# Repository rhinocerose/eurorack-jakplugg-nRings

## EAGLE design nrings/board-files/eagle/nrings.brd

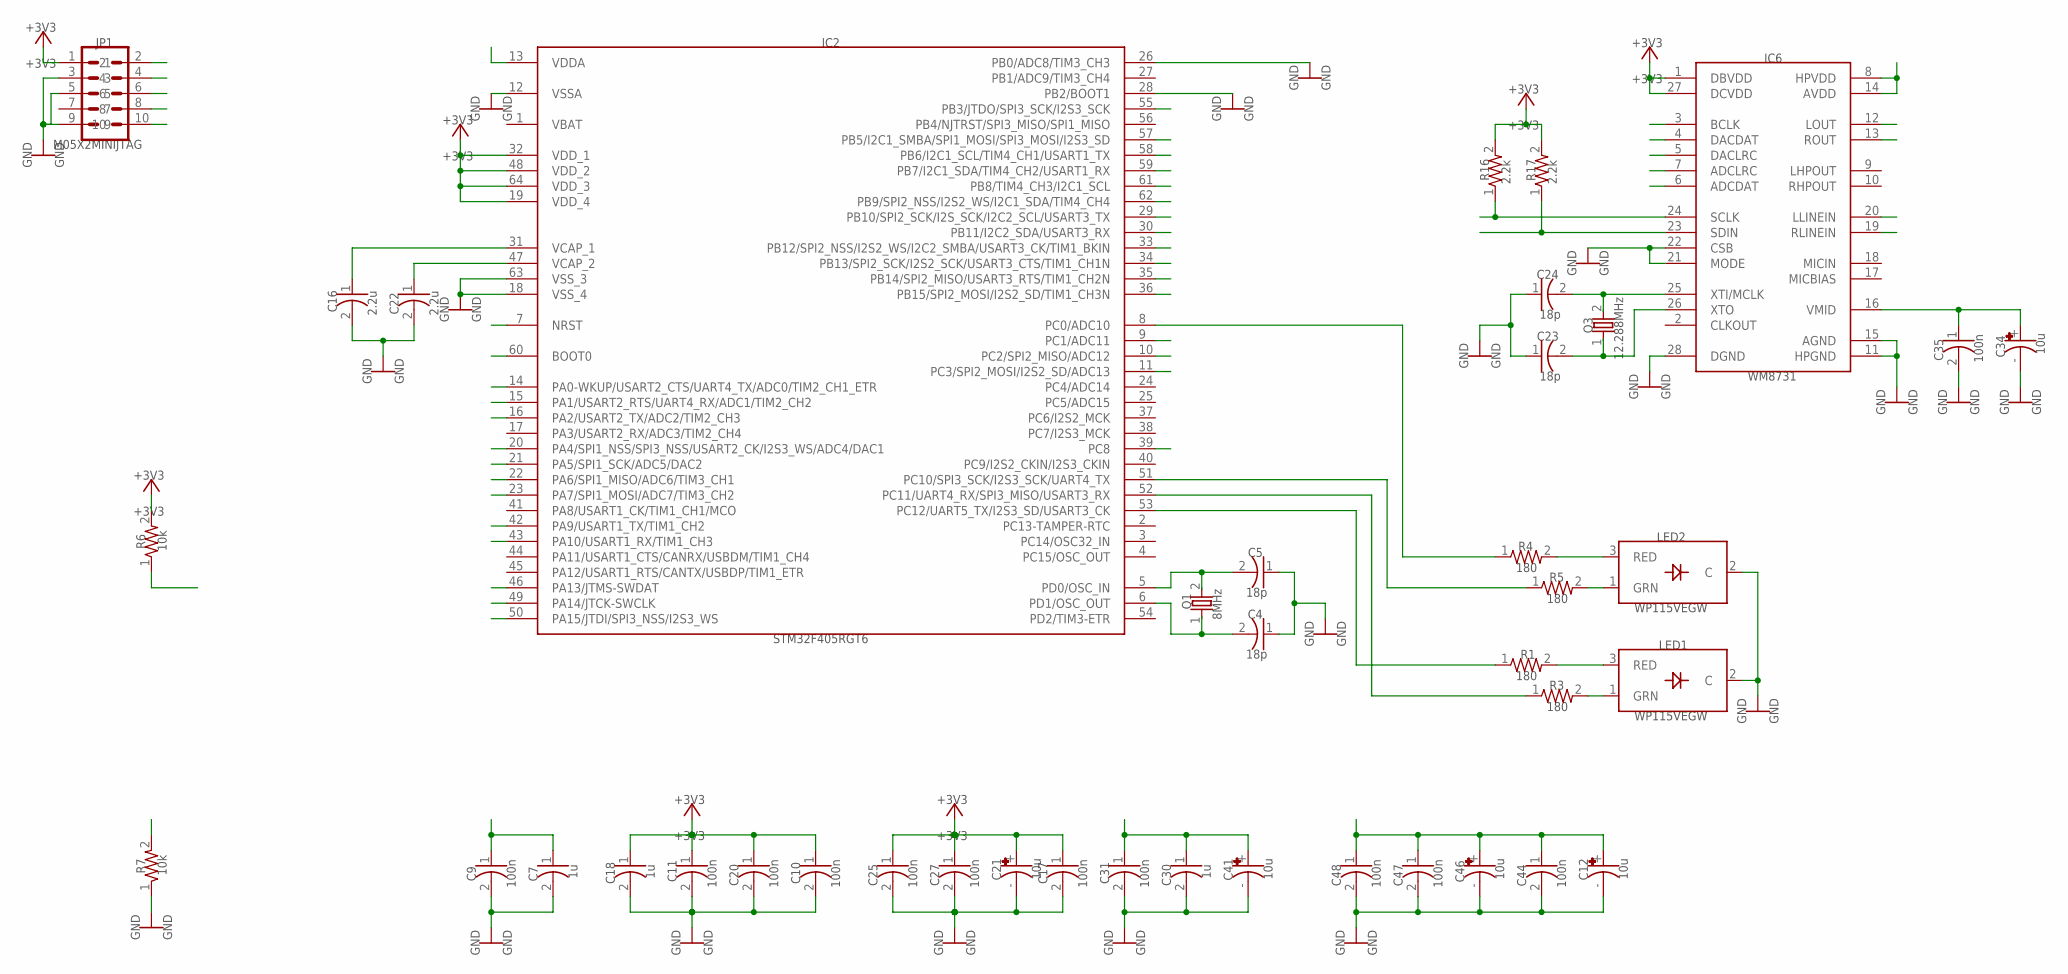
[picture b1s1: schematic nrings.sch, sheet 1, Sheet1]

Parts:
C4, C5, C23, C24: 18p; CAP_0603
C7, C18, C30: 1u; CAP_0603
C9, C10, C11, C17, C20, C25, C27, C31, C35, C44, C47, C48: 100n; CAP_0603
C12, C21, C34, C41, C46: 10u; PANASONIC_A
C16, C22: 2.2u; CAP_0805
IC2: STM32F405RGT6; TQFP-10X10-64
IC6: WM8731; SSOP28
JP1: M05X2MINIJTAG; 2X5-1.27
LED1, LED2: WP115VEGW; LED-BICOLOR-THROUGHHOLE
Q1: 8MHz; TSC_7A_CRYSTAL
Q3: 12.288MHz; TSC_7A_CRYSTAL
R1, R3, R4, R5: 180; RES_0603
R6, R7: 10k; RES_0603
R16, R17: 2.2k; RES_0603

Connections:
+3V3: C10.1, C11.1, C17.1, C18.1, C20.1, C21.+, C25.1, C27.1, IC2.19 (VDD_4), IC2.32 (VDD_1), IC2.48 (VDD_2), IC2.64 (VDD_3), IC6.1 (DBVDD), IC6.27 (DCVDD), JP1.1, R6.2, R16.2, R17.2; also elsewhere on the board
+3V3_A: C7.1, C9.1, C12.+, C30.1, C31.1, C41.+, C44.1, C46.+, C47.1, C48.1, IC2.13 (VDDA), IC6.8 (HPVDD), IC6.14 (AVDD); also elsewhere on the board
AUX_OUT: IC6.13 (ROUT); also elsewhere on the board
BOOT_FLASH: IC2.60 (BOOT0), R7.2
BRIGHTNESS_CV: IC2.14 (PA0-WKUP/USART2_CTS/UART4_TX/ADC0/TIM2_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); also elsewhere on the board
DAMP_CV: IC2.21 (PA5/SPI1_SCK/ADC5/DAC2); also elsewhere on the board
FM_CV: IC2.20 (PA4/SPI1_NSS/SPI3_NSS/USART2_CK/I2S3_WS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); also elsewhere on the board
FREQUENCY_POT: IC2.11 (PC3/SPI2_MOSI/I2S2_SD/ADC13); also elsewhere on the board
GEOMETRY_CV: IC2.22 (PA6/SPI1_MISO/ADC6/TIM3_CH1); also elsewhere on the board
GEOMETRY_POT: IC2.10 (PC2/SPI2_MISO/ADC12); also elsewhere on the board
GND: C4.1, C5.1, C7.2, C9.2, C10.2, C11.2, C12.-, C16.2, C17.2, C18.2, C20.2, C21.-, C22.2, C23.1, C24.1, C25.2, C27.2, C30.2, C31.2, C34.-, C35.2, C41.-, C44.2, C46.-, C47.2, C48.2, IC2.12 (VSSA), IC2.18 (VSS_4), IC2.26 (PB0/ADC8/TIM3_CH3), IC2.28 (PB2/BOOT1), IC2.63 (VSS_3), IC6.11 (HPGND), IC6.15 (AGND), IC6.21 (MODE), IC6.22 (CSB), IC6.28 (DGND), JP1.3, JP1.5, JP1.9, LED1.2 (C), LED2.2 (C), R7.1; also elsewhere on the board
I2C_SCL: IC2.29 (PB10/SPI2_SCK/I2S_SCK/I2C2_SCL/USART3_TX), IC6.24 (SCLK), R16.1
I2C_SDA: IC2.30 (PB11/I2C2_SDA/USART3_RX), IC6.23 (SDIN), R17.1
I2S_LRCK: IC2.33 (PB12/SPI2_NSS/I2S2_WS/I2C2_SMBA/USART3_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), IC6.5 (DACLRC), IC6.7 (ADCLRC)
I2S_SCK: IC2.34 (PB13/SPI2_SCK/I2S2_SCK/USART3_CTS/TIM1_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), IC6.3 (BCLK)
I2S_SIN: IC2.35 (PB14/SPI2_MISO/USART3_RTS/TIM1_CH2N), IC6.6 (ADCDAT)
I2S_SOUT: IC2.36 (PB15/SPI2_MOSI/I2S2_SD/TIM1_CH3N), IC6.4 (DACDAT)
IN_1: IC6.20 (LLINEIN); also elsewhere on the board
IN_2: IC6.19 (RLINEIN); also elsewhere on the board
JTCK: IC2.49 (PA14/JTCK-SWCLK), JP1.4
JTDI: IC2.50 (PA15/JTDI/SPI3_NSS/I2S3_WS), JP1.8
JTDO: IC2.55 (PB3/JTDO/SPI3_SCK/I2S3_SCK), JP1.6
JTMS: IC2.46 (PA13/JTMS-SWDAT), JP1.2
MAIN_OUT: IC6.12 (LOUT); also elsewhere on the board
MUXED_POTS: IC2.9 (PC1/ADC11); also elsewhere on the board
MUX_ADDR_0: IC2.59 (PB7/I2C1_SDA/TIM4_CH2/USART1_RX); also elsewhere on the board
MUX_ADDR_1: IC2.58 (PB6/I2C1_SCL/TIM4_CH1/USART1_TX); also elsewhere on the board
MUX_ADDR_2: IC2.57 (PB5/I2C1_SMBA/SPI1_MOSI/SPI3_MOSI/I2S3_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); also elsewhere on the board
unnamed: C5.2, IC2.5 (PD0/OSC_IN), Q1.2
unnamed: C4.2, IC2.6 (PD1/OSC_OUT), Q1.1
unnamed: LED1.3 (RED), R1.2
unnamed: C22.1, IC2.47 (VCAP_2)
unnamed: C34.+, C35.1, IC6.16 (VMID)
unnamed: C16.1, IC2.31 (VCAP_1)
unnamed: LED1.1 (GRN), R3.2
unnamed: LED2.3 (RED), R4.2
unnamed: LED2.1 (GRN), R5.2
unnamed: IC2.52 (PC11/UART4_RX/SPI3_MISO/USART3_RX), R3.1
unnamed: IC2.8 (PC0/ADC10), R4.1
unnamed: C24.2, IC6.25 (XTI/MCLK), Q3.2
unnamed: C23.2, IC6.26 (XTO), Q3.1
unnamed: IC2.53 (PC12/UART5_TX/I2S3_SD/USART3_CK), R1.1
unnamed: IC2.51 (PC10/SPI3_SCK/I2S3_SCK/UART4_TX), R5.1
NORMALIZATION_PROBE: IC2.39 (PC8); also elsewhere on the board
POSITION_CV: IC2.23 (PA7/SPI1_MOSI/ADC7/TIM3_CH2); also elsewhere on the board
RESET: IC2.7 (NRST), JP1.10, R6.1
STRUM: IC2.16 (PA2/USART2_TX/ADC2/TIM2_CH3); also elsewhere on the board
SW_MODE: IC2.61 (PB8/TIM4_CH3/I2C1_SCL); also elsewhere on the board
SW_POLYPHONY: IC2.62 (PB9/SPI2_NSS/I2S2_WS/I2C1_SDA/TIM4_CH4); also elsewhere on the board
V_OCT_CV: IC2.15 (PA1/USART2_RTS/UART4_RX/ADC1/TIM2_CH2); also elsewhere on the board

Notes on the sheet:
+3V3
18p
100n
C10
C11
C12
10u
C16
2.2u
C17
C18
C20
C21
C22
C23
C24
C25
C27
C30
C31
C34
C35
C41
C44
C46
C47
C48
GND
IC2
STM32F405RGT6
IC6
WM8731
JP1
M05X2MINIJTAG
LED1
WP115VEGW
LED2
8MHz
12.288MHz
180

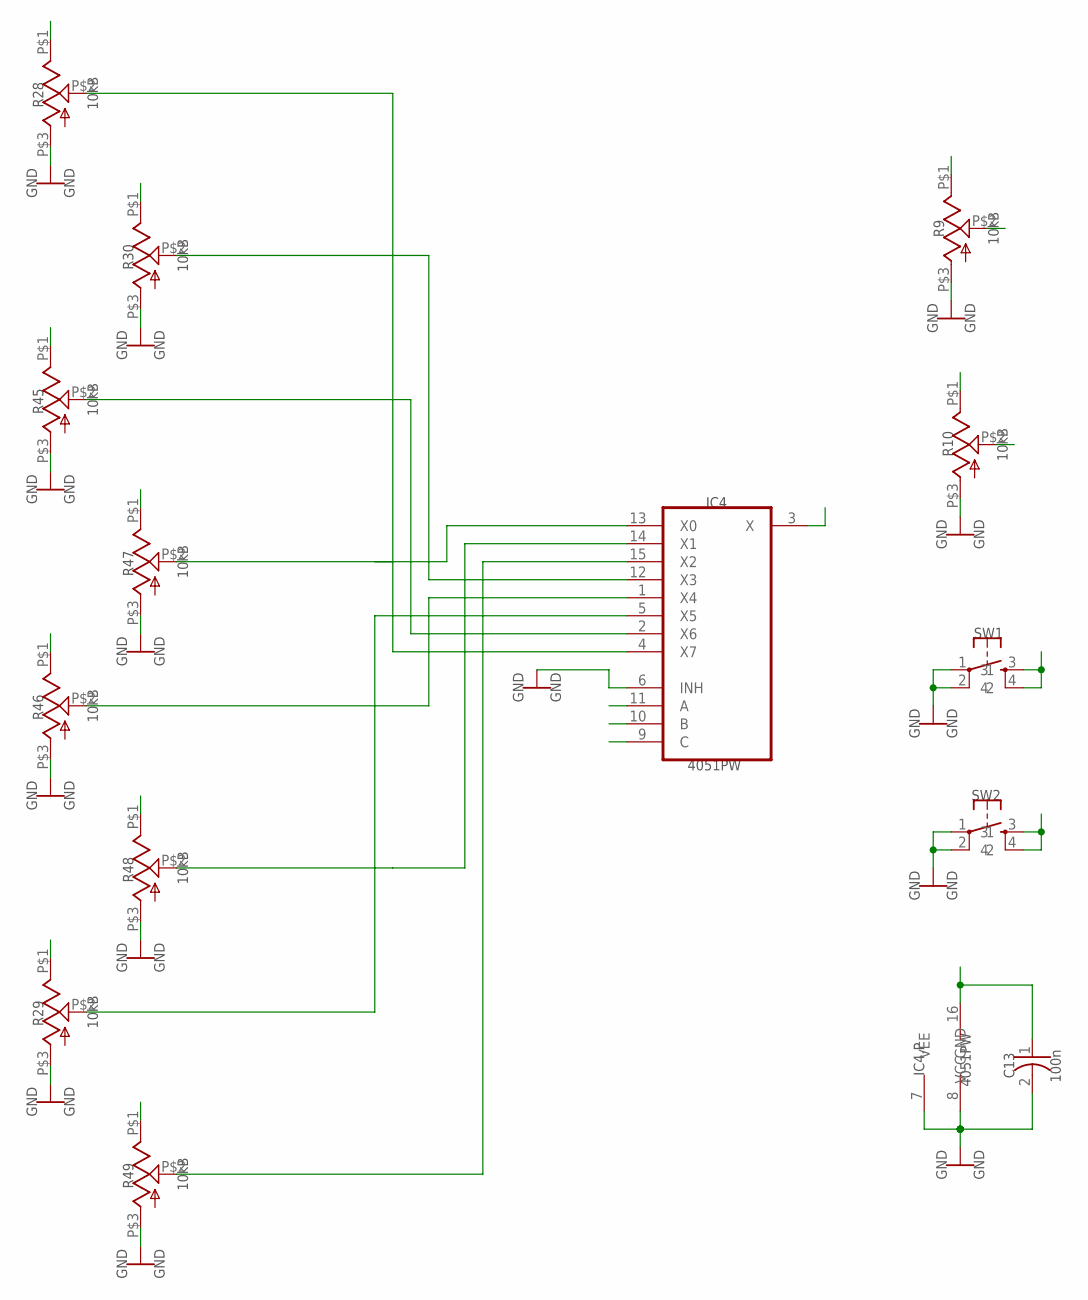
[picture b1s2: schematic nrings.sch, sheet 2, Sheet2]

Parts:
C13: 100n; CAP_0603
IC4: 4051PW; TSSOP16
R9, R10, R28, R29, R30: 10kB; ALPS_POT_VERTICAL_PS
R45, R46, R47, R48, R49: 10kB; ALPS_POT_VERTICAL
SW1, SW2: TAC_SWITCHPTH; TACTILE-PTH

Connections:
+3V3_A: C13.1, IC4.16 (VCC), R9.P$1 (E), R10.P$1 (E), R28.P$1 (E), R29.P$1 (E), R30.P$1 (E), R45.P$1 (E), R46.P$1 (E), R47.P$1 (E), R48.P$1 (E), R49.P$1 (E); also elsewhere on the board
BRIGHTNESS_ATT: IC4.2 (X6), R45.P$2 (S)
BRIGHTNESS_POT: IC4.4 (X7), R28.P$2 (S)
DAMP_ATT: IC4.13 (X0), R47.P$2 (S)
DAMP_POT: IC4.5 (X5), R29.P$2 (S)
FREQUENCY_ATT: IC4.1 (X4), R46.P$2 (S)
FREQUENCY_POT: R9.P$2 (S); also elsewhere on the board
GEOMETRY_ATT: IC4.14 (X1), R48.P$2 (S)
GEOMETRY_POT: R10.P$2 (S); also elsewhere on the board
GND: C13.2, IC4.6 (INH), IC4.7 (VEE), IC4.8 (GND), R9.P$3 (A), R9.P$4, R9.P$5, R10.P$3 (A), R10.P$4, R10.P$5, R28.P$3 (A), R28.P$4, R28.P$5, R29.P$3 (A), R29.P$4, R29.P$5, R30.P$3 (A), R30.P$4, R30.P$5, R45.P$3 (A), R45.P$4, R45.P$5, R46.P$3 (A), R46.P$4, R46.P$5, R47.P$3 (A), R47.P$4, R47.P$5, R48.P$3 (A), R48.P$4, R48.P$5, R49.P$3 (A), R49.P$4, R49.P$5, SW1.1, SW1.2, SW2.1, SW2.2; also elsewhere on the board
MUXED_POTS: IC4.3 (X); also elsewhere on the board
MUX_ADDR_0: IC4.11 (A); also elsewhere on the board
MUX_ADDR_1: IC4.10 (B); also elsewhere on the board
MUX_ADDR_2: IC4.9 (C); also elsewhere on the board
POSITION_ATT: IC4.15 (X2), R49.P$2 (S)
POSITION_POT: IC4.12 (X3), R30.P$2 (S)
SW_MODE: SW2.3, SW2.4; also elsewhere on the board
SW_POLYPHONY: SW1.3, SW1.4; also elsewhere on the board

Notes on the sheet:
C13
100n
GND
IC4
4051PW
IC4.P
10kB
R10
R28
R29
R30
R45
R46
R47
R48
R49
SW1
SW2

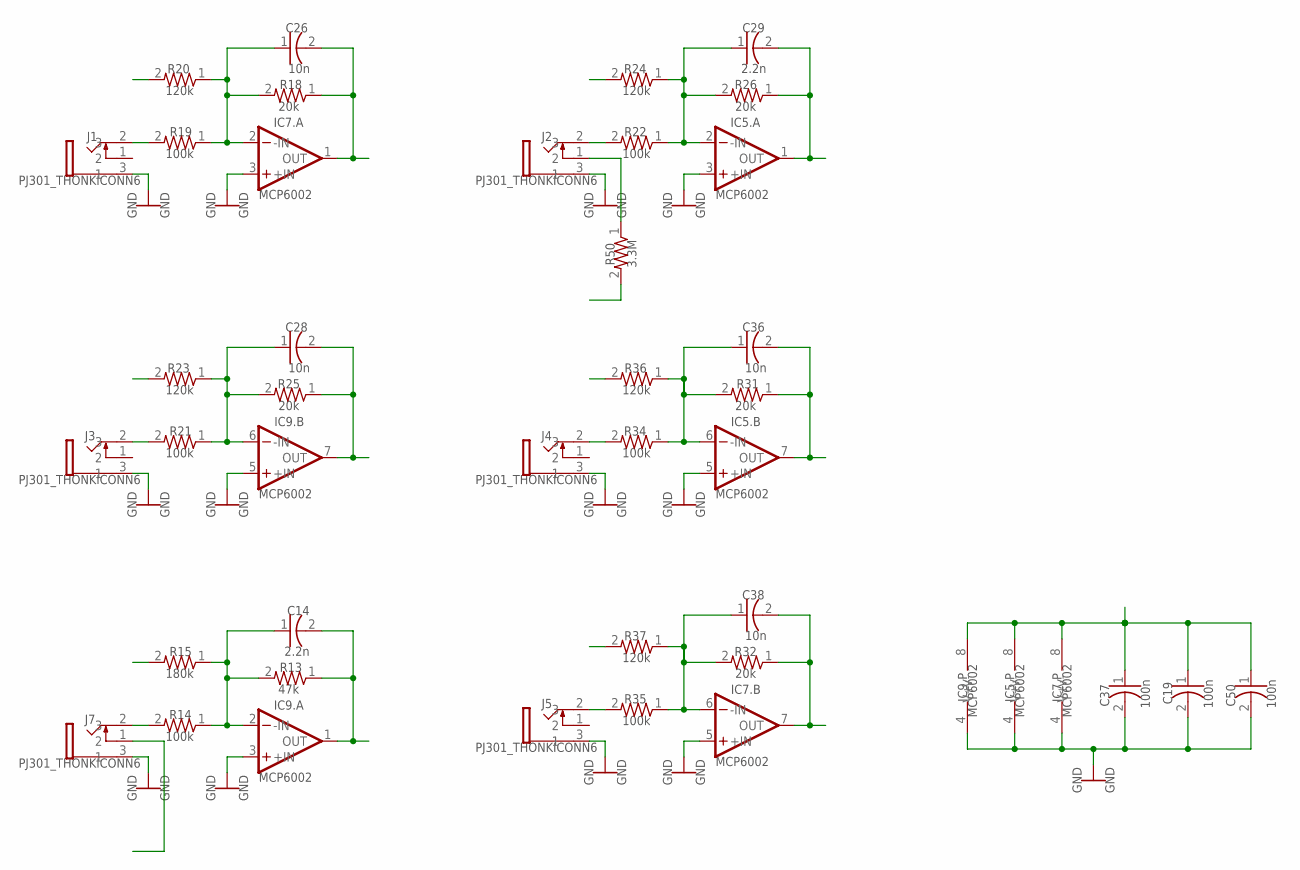
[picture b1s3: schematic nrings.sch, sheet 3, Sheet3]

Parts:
C14, C29: 2.2n; CAP_0603
C19, C37, C50: 100n; CAP_0603
C26, C28, C36, C38: 10n; CAP_0603
IC5, IC7, IC9: MCP6002; SO08
J1, J2, J3, J4, J5, J7: PJ301_THONKICONN6; THONKICONN
R13: 47k; RES_0603
R14, R19, R21, R22, R34, R35: 100k; RES_0603
R15: 180k; RES_0603
R18, R25, R26, R31, R32: 20k; RES_0603
R20, R23, R24, R36, R37: 120k; RES_0603
R50: 3.3M; RES_0603

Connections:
+3V3_A: C19.1, C37.1, C50.1, IC5.8 (V+), IC7.8 (V+), IC9.8 (V+), R50.2; also elsewhere on the board
AREF_-10: R15.2, R20.2, R23.2, R24.2, R36.2, R37.2; also elsewhere on the board
BRIGHTNESS_CV: C26.2, IC7.1 (OUT), R18.1; also elsewhere on the board
CV_NORMALIZATION: J7.1 (2); also elsewhere on the board
DAMP_CV: C28.2, IC9.7 (OUT), R25.1; also elsewhere on the board
FM_CV: C29.2, IC5.1 (OUT), R26.1; also elsewhere on the board
GEOMETRY_CV: C36.2, IC5.7 (OUT), R31.1; also elsewhere on the board
GND: C19.2, C37.2, C50.2, IC5.3 (+IN), IC5.4 (V-), IC5.5 (+IN), IC7.3 (+IN), IC7.4 (V-), IC7.5 (+IN), IC9.3 (+IN), IC9.4 (V-), IC9.5 (+IN), J1.3 (1), J2.3 (1), J3.3 (1), J4.3 (1), J5.3 (1), J7.3 (1); also elsewhere on the board
unnamed: J1.2 (3), R19.2
unnamed: C26.1, IC7.2 (-IN), R18.2, R19.1, R20.1
unnamed: J7.2 (3), R14.2
unnamed: J2.2 (3), R22.2
unnamed: C29.1, IC5.2 (-IN), R22.1, R24.1, R26.2
unnamed: J4.2 (3), R34.2
unnamed: J3.2 (3), R21.2
unnamed: C28.1, IC9.6 (-IN), R21.1, R23.1, R25.2
unnamed: C14.1, IC9.2 (-IN), R13.2, R14.1, R15.1
unnamed: C36.1, IC5.6 (-IN), R31.2, R34.1, R36.1
unnamed: J5.2 (3), R35.2
unnamed: C38.1, IC7.6 (-IN), R32.2, R35.1, R37.1
unnamed: J2.1 (2), R50.1
POSITION_CV: C38.2, IC7.7 (OUT), R32.1; also elsewhere on the board
V_OCT_CV: C14.2, IC9.1 (OUT), R13.1; also elsewhere on the board

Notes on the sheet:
C14
2.2n
C19
100n
C26
10n
C28
C29
C36
C37
C38
C50
GND
IC5.A
MCP6002
IC5.B
IC5.P
IC7.A
IC7.B
IC7.P
IC9.A
IC9.B
IC9.P
PJ301_THONKICONN6
R13
47k
R14
100k
R15
180k
R18
20k
R19
R20
120k
R21
R22
R23
R24
R25

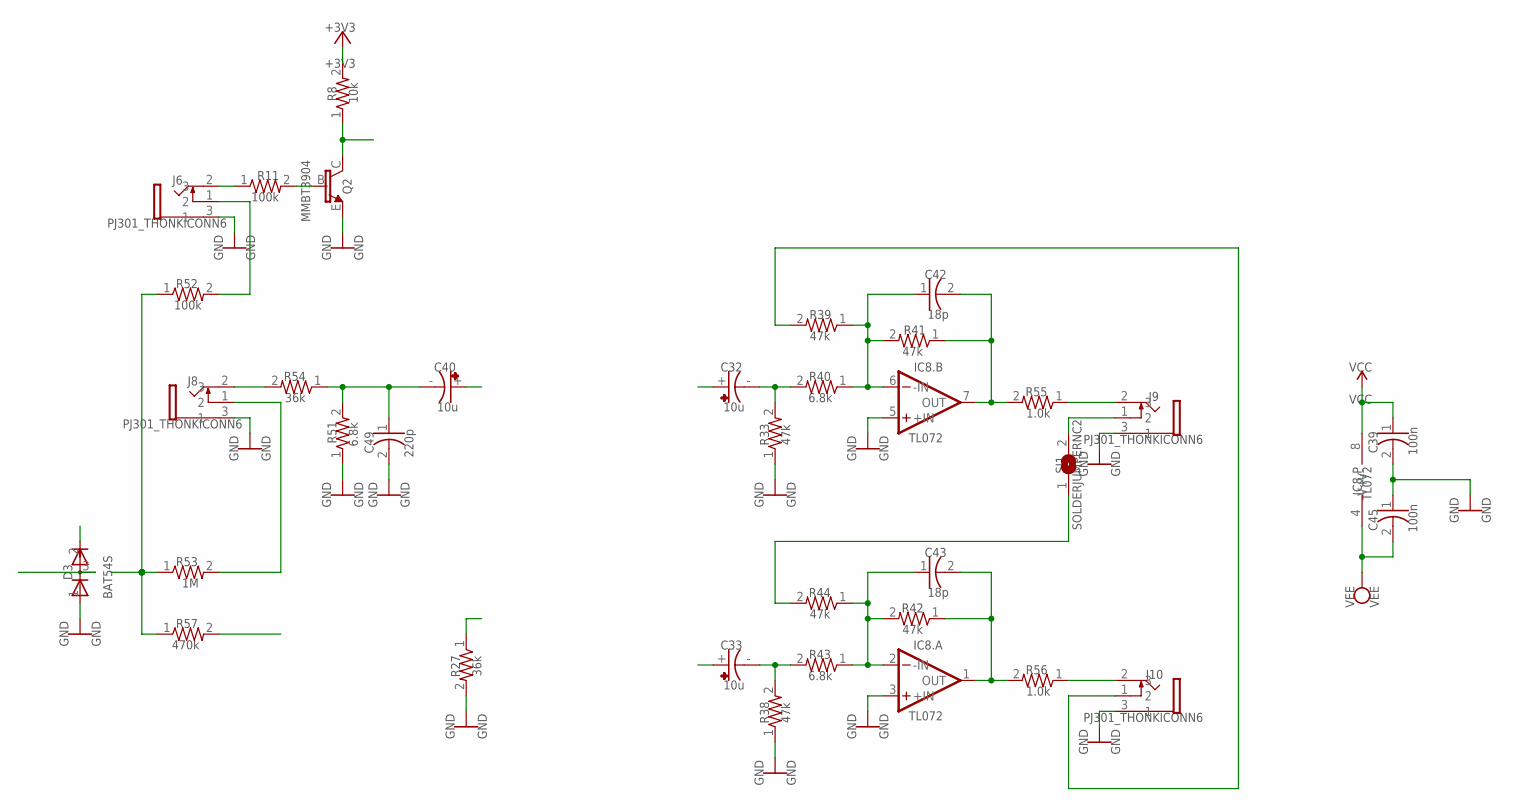
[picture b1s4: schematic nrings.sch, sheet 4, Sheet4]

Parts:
C32, C33, C40: 10u; PANASONIC_A
C39, C45: 100n; CAP_0603
C42, C43: 18p; CAP_0603
C49: 220p; CAP_0603
D3: BAT54S; SOT23
IC8: TL072; SO08
J6, J8, J9, J10: PJ301_THONKICONN6; THONKICONN
Q2: MMBT3904; SOT23-BEC
R8: 10k; RES_0603
R11, R52: 100k; RES_0603
R27, R54: 36k; RES_0603
R33, R38, R39, R41, R42, R44: 47k; RES_0603
R40, R43, R51: 6.8k; RES_0603
R53: 1M; RES_0603
R55, R56: 1.0k; RES_0603
R57: 470k; RES_0603
SJ1: SOLDERJUMPERNC2; SJ_2S-NOTRACE

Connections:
+3V3: D3.2 (C), R8.2; also elsewhere on the board
AUX_OUT: C33.+; also elsewhere on the board
CV_NORMALIZATION: R57.2; also elsewhere on the board
GND: C39.2, C45.1, C49.2, D3.1 (A), IC8.3 (+IN), IC8.5 (+IN), J6.3 (1), J8.3 (1), J9.3 (1), J10.3 (1), Q2.E, R27.2, R33.1, R38.1, R51.1; also elsewhere on the board
IN_1: R27.1; also elsewhere on the board
IN_2: C40.+; also elsewhere on the board
MAIN_OUT: C32.+; also elsewhere on the board
unnamed: J6.2 (3), R11.1
unnamed: C40.-, C49.1, R51.2, R54.1
unnamed: J6.1 (2), R52.2
unnamed: J8.2 (3), R54.2
unnamed: C33.-, R38.2, R43.2
unnamed: C43.1, IC8.2 (-IN), R42.2, R43.1, R44.1
unnamed: C43.2, IC8.1 (OUT), R42.1, R56.2
unnamed: J10.2 (3), R56.1
unnamed: C32.-, R33.2, R40.2
unnamed: C42.1, IC8.6 (-IN), R39.1, R40.1, R41.2
unnamed: C42.2, IC8.7 (OUT), R41.1, R55.2
unnamed: J9.2 (3), R55.1
unnamed: J8.1 (2), R53.2
unnamed: J10.1 (2), R39.2
unnamed: R44.2, SJ1.1
unnamed: J9.1 (2), SJ1.2
unnamed: Q2.B, R11.2
NORMALIZATION_PROBE: D3.3 (AC), R52.1, R53.1, R57.1; also elsewhere on the board
STRUM: Q2.C, R8.1; also elsewhere on the board
VCC: C39.1, IC8.8 (V+); also elsewhere on the board
VEE: C45.2, IC8.4 (V-); also elsewhere on the board

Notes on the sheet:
+3V3
C32
10u
C33
C39
100n
C40
C42
18p
C43
C45
C49
220p
BAT54S
GND
IC8.A
TL072
IC8.B
IC8.P
PJ301_THONKICONN6
J10
VCC
MMBT3904
10k
R11
100k
R27
36k
R33
47k
R38
R39
R40
6.8k
R41
R42
R43
R44
R51
R52

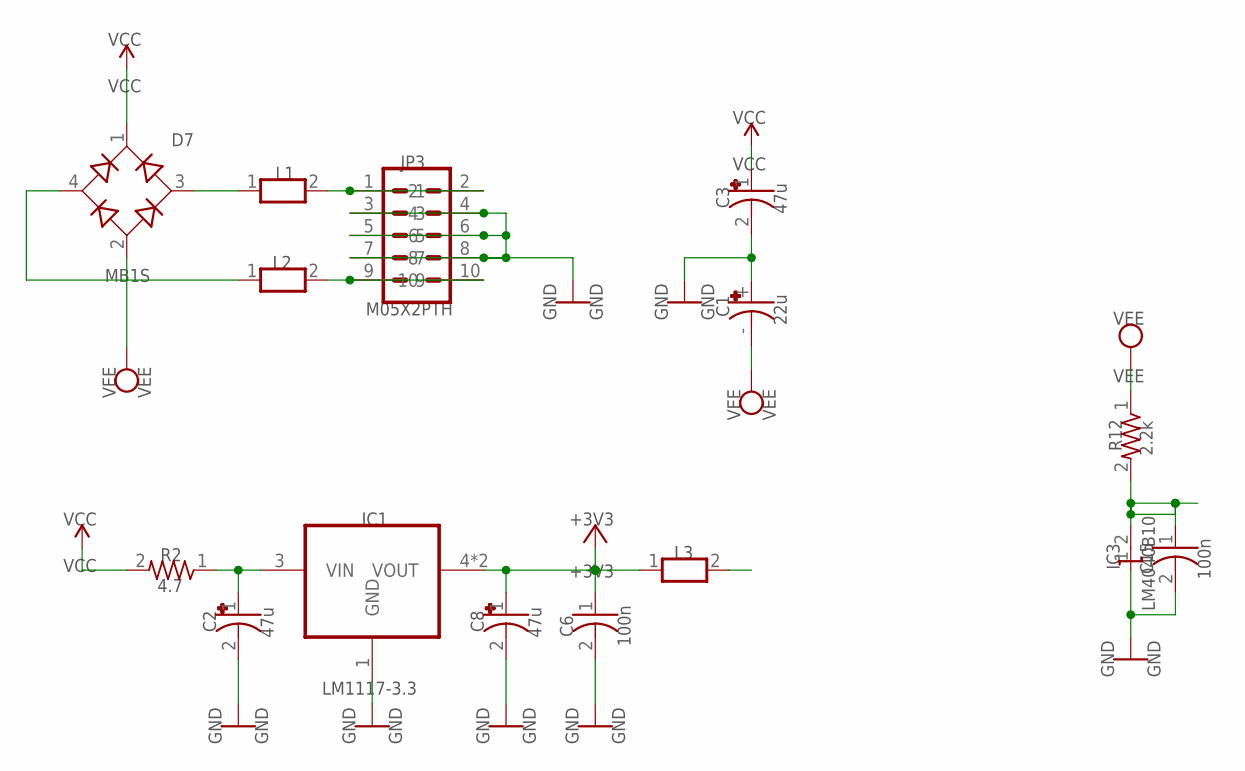
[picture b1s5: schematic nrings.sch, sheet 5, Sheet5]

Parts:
C1: 22u; PANASONIC_C
C2, C3, C8: 47u; CAPAE-5.3X5.3H7
C6, C15: 100n; CAP_0603
D7: MB1S; SOP-4/6.5X2.54
IC1: LM1117-3.3; SOT223-4
IC3: LM4040B10; DBZ_R-PDSO-G3
JP3: M05X2PTH; AVR_ICSP
L1, L2, L3: WE-CBF_0603; 0603
R2: 4.7; R1206
R12: 2.2k; RES_0603

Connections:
+3V3: C6.1, C8.1 (+), IC1.2 (VOUT), IC1.4 (VOUT), L3.1; also elsewhere on the board
+3V3_A: L3.2; also elsewhere on the board
AREF_-10: C15.1, IC3.2 (A), R12.2; also elsewhere on the board
GND: C1.+, C2.2 (-), C3.2 (-), C6.2, C8.2 (-), C15.2, IC1.1 (GND), IC3.1 (C), JP3.3, JP3.4, JP3.5, JP3.6, JP3.7, JP3.8; also elsewhere on the board
unnamed: C2.1 (+), IC1.3 (VIN), R2.1
unnamed: JP3.1, JP3.2, L1.2
unnamed: JP3.9, JP3.10, L2.2
Net_95: D7.3 (AC2), L1.1
Net_96: D7.4 (AC1), L2.1
VCC: C3.1 (+), D7.1 (+), R2.2; also elsewhere on the board
VEE: C1.-, D7.2 (-), R12.1; also elsewhere on the board

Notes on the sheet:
+3V3
22u
47u
100n
C15
MB1S
GND
IC1
LM1117-3.3
IC3
LM4040B10
JP3
M05X2PTH
VCC
4.7
R12
2.2k
VEE

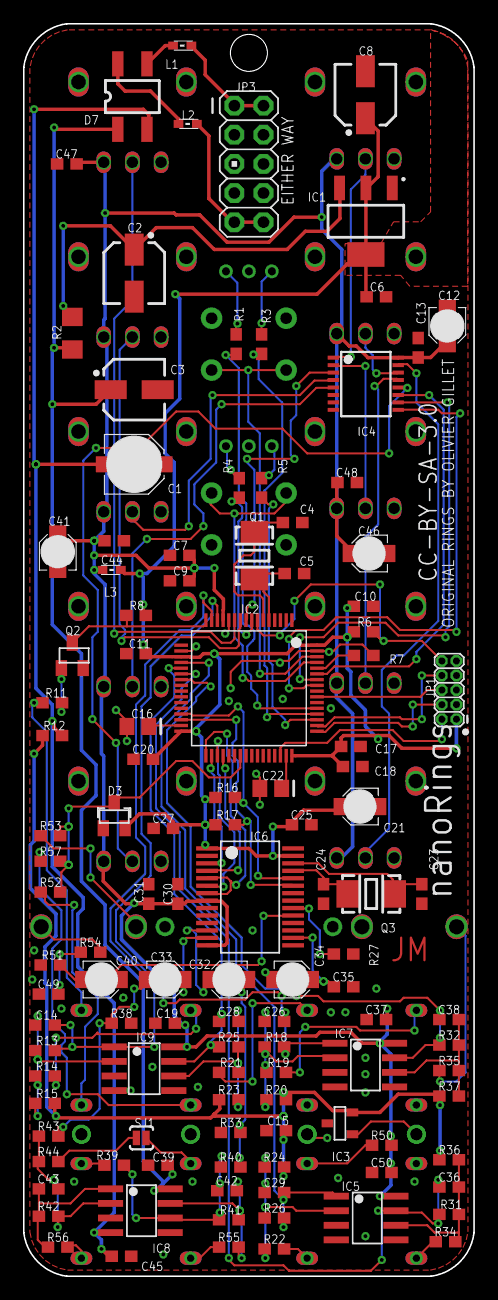
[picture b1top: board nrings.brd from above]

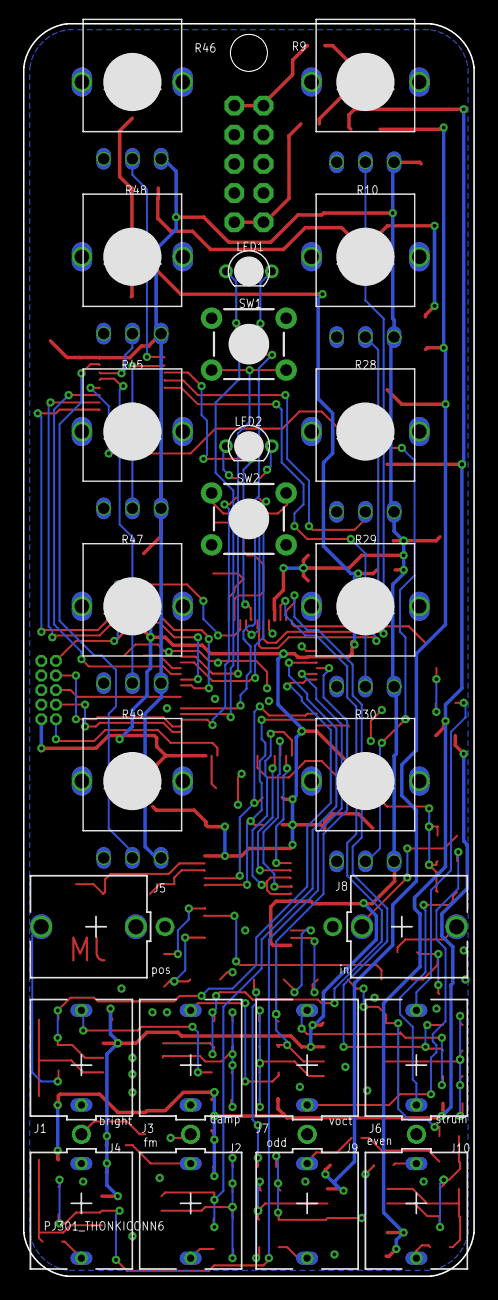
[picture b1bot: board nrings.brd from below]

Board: 2 copper layers, 39.3 x 109.2 mm, 141 parts (24 on the bottom side), 97 nets.

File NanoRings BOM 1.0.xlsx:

Quantity | Value | RefDes | Name | Mouser | Other | Notes
6.0 | 18p | C4, C5, C23, C24, C42, C43 | C-USC0603 | 81-GRM185C1H180JA01J
1.0 | 220p | C49 | C-USC0603 | 81-GRM185C1H221GA01D
2.0 | 2.2n | C14, C29 | C-USC0603 | 81-GRM1885C1H222JA1J
4.0 | 10n | C26, C28, C36, C38 | C-USC0603 | 81-GRM18R71H103JA01D
20.0 | 100n | C6, C9, C10, C11, C13, C15, C17, C19, C20, C25, C27, C31, C35, C37, C39, C44, C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 | C-USC0603 | 81-GRM188R71E104JA1J
3.0 | 1u | C7, C18, C30 | C-USC0603 | 81-GRM18R61A105KA61J
2.0 | 2.2u | C16, C22 | C-USC0805 | 810-C2012X5R1A225K-2
8.0 | 10u | C12, C21, C32, C33, C34, C40, C41, C46 | CPOL-USA | 647-UWX1C100MCL2
1.0 | 22u | C1 | CPOL-USC | 667-EEE-FP1E220AR
3.0 | 47u | C2, C3, C8 | CPOL-USD | 667-EEE-FT1V470AR
1.0 | 4.7 | R2 | R-US_R1206 | 603-RC1206JR-074R7L
4.0 | 180.0 | R1, R3, R4, R5 | R-US_R0603 | 603-RC0603FR-07180RL
2.0 | 1.0k | R55, R56 | R-US_R0603 | 603-RC0603FR-071KL
3.0 | 2.2k | R12, R16, R17 | R-US_R0603 | 603-RC0603FR-072K2L
3.0 | 6.8k | R40, R43, R51 | R-US_R0603 | 603-RC0603FR-076K8L
3.0 | 10k | R6, R7, R8 | R-US_R0603 | 603-RC0603FR-0710KL
5.0 | 20k | R18, R25, R26, R31, R32 | R-US_R0603 | 603-RC0603FR-0720KL
2.0 | 36k | R27, R54 | R-US_R0603 | 603-RC0603FR-0736KL
7.0 | 47k | R13, R33, R38, R39, R41, R42, R44 | R-US_R0603 | 603-RC0603FR-0747KL
8.0 | 100k | R11, R14, R19, R21, R22, R34, R35, R52 | R-US_R0603 | 603-RC0603FR-07100KL
5.0 | 120k | R20, R23, R24, R36, R37 | R-US_R0603 | 603-RC0603FR-07120KL
1.0 | 180k | R15 | R-US_R0603 | 603-RC0603FR-07180KL
1.0 | 470k | R57 | R-US_R0603 | 603-RC0603FR-07470KL
1.0 | 1M | R53 | R-US_R0603 | 603-RC0603FR-071ML
1.0 | 3.3M | R50 | R-US_R0603 | RC0603FR-073M3L
5.0 | 10kB | R45, R46, R47, R48, R49 | POT_USVERTICAL | Sung Huei Short
5.0 | 10kB | R9, R10, R28, R29, R30 | POT_USVERTICAL_PS | Sung Huei Long
1.0 | BAT54S | D3 | DIODE_2CACA-SOT23 | 512-BAT54S
1.0 | MB1S | D7 | MB1S | 512-MB1S
1.0 | LM1117-3.3 | IC1 | REG1117T | 926-LM1117MPX3.3NOPB
1.0 | STM32F405RGT6 | IC2 | STM32F20X | 511-STM32F405RGT6
1.0 | LM4040B10 | IC3 | LM4041B12DBZ | 595-LM4040C10IDBZR
1.0 | 4051PW | IC4 | 4051PW | 595-CD4051BPWR
3.0 | MCP6002 | IC5, IC7, IC9 | SOIC8 | 579-MCP6002-I/SN
1.0 | WM8731 | IC6 | WM8731 | 238-WM8731SEDS/V
1.0 | TL072 | IC8 | SOIC8 | 595-TL072CD
3.0 |  | L1, L2, L3 | WE-CBF_0603 | 710-742792642
2.0 | WP115VEGW | LED1, LED2 | LED-BICOLOR-TH | 604-WP115VEGW
1.0 | 8MHz | Q1 | TSC 7A crystal | 717-7A-8.000MAAJ-T
1.0 | MMBT3904 | Q2 | MMBT3904 | 863-MMBT3904LT1G
1.0 | 12.288MHz | Q3 | TSC 7A crystal | 717-7A-12.288MAAJ-T
2.0 |  | SW1, SW2 | TAC_SWITCHPTH | 612-TL1105SP-250
2.0 |  |  | Cap for switch | 612-1R-BK
10.0 | PJ301 | J1, J2, J3, J4, J5, J6, J7, J8. J9, J10
1.0 | SOLDERJUMPERNC2 | SJ1 | SOLDERJUMPERNC2
1.0 | M05X2MINIJTAG | JP1 | M05X2MINIJTAG
1.0 | M05X2PTH | JP3 | M05X2PTH

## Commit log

2025-08-07 converted to eagle
2025-08-07 Kicad

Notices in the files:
nrings/board-files/eagle/nrings.brd:
CC-BY-SA-3.0
